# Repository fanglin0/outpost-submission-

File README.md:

# FIFA World Cup Player Love Compatibility Test

##  What this project is
Inspired by <a href="https://www.reddit.com/r/AustralianNostalgia/comments/1fx5e6g/old_school_love_compatibility_tests_random_i_know/">old school romance compaitbility tests (based on names)</a> I built a old-school style, hand-held console like hardware with Arduino 32 as the display to match the player to their soulmate (from the cast of the 2026 FIFA world cup players trending all over social media). With a series of personality questions the user will be matched to their perfect partner from the world cup, and be able to navigate and reset through answer choices with the buttons.

The Arduino handles the logic, the PCB wires everything together, and the OLED will display the game alongisde the buttons. 

## Project Architecture
                USB-C
                   │
                   ▼
        ┌─────────────────┐
        │ Arduino Nano    │
        │ ESP32           │
        │                 │
        │ Runs all code   │
        └─────────────────┘
           │  │  │  │
           │  │  │  │
           │  │  │  └── D5 → RESET button
           │  │  └───── D4 → RIGHT button
           │  └──────── D3 → OK button
           └─────────── D2 → LEFT button

           │
           ├── SDA → OLED SDA
           └── SCL → OLED SCL

           │
           ├── 5V → OLED VCC
           └── GND → OLED GND

## Software Flow 
Power On
   │
   ▼
Title Screen
   │
   ▼
Intro Screen
   │
   ▼
12 Quiz Questions
   │
   ▼
Fake Analysis Screen
   │
   ▼
Compatibility Result
   │
   ▼
Football Profile
   │
   ▼
Ending Screen
   │
   ▼
Reset

## Image examples and Demo
<a href="https://youtu.be/Up6vLfFCHvI">Video demo here</a>

---

## Why I made this project
To learn hardware in a unique project that I would enjoy using myself!

## How I made this project

Followed various tutorials for kicad, the C tutoial for eprosnality quiz to script the logic behind the love compatiblity quiz, and then learning how to use onshape to rig a simple 3d case to make the model resemble my vision of a handheld console more.

---

## Challenges I faced
Trying to get the LONG script to come together, had to troubleshoot various times
Also, trying to 3d model in onshape. I struggled to navigate the basic menu and a lot of parts in the project was harder than expected, as I had to learn them from scratch. It took a lot more cramming than expected to get in before deadline :')

##AI Declaration
ChatGPT was used to debug code when I got stuck, as I'm a complete beginner with almost no background in hardware.

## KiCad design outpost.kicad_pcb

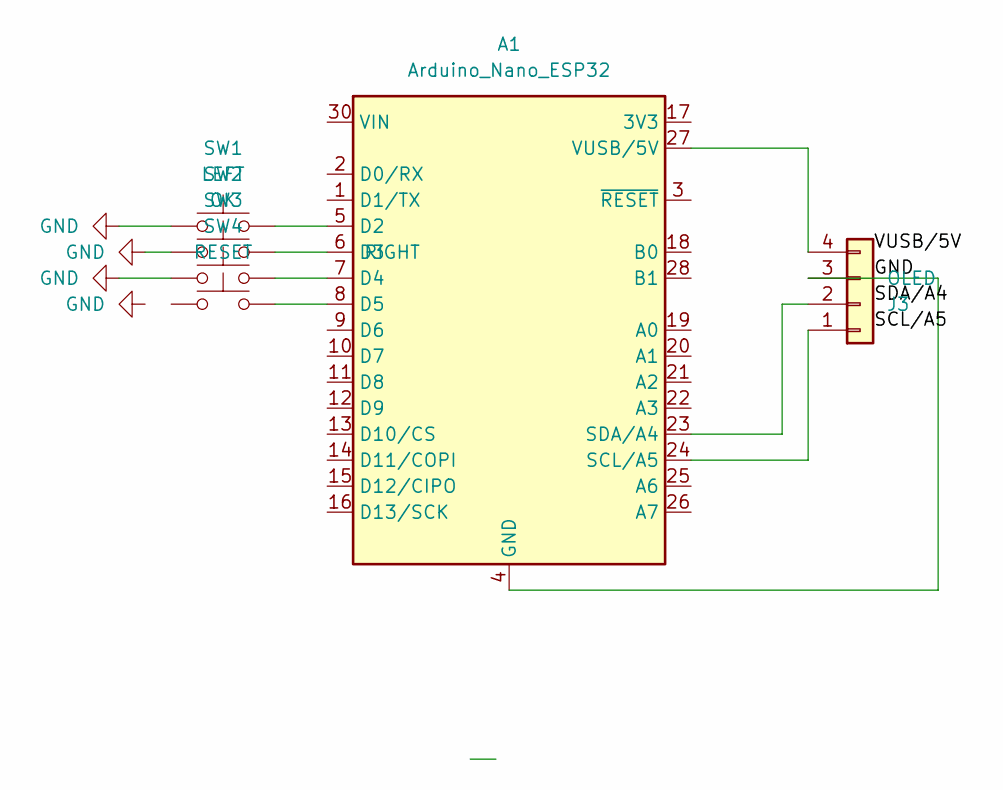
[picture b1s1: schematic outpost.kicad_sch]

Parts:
A1: Arduino_Nano_ESP32; PinHeader_2x15_P1.00mm_Horizontal
J3: OLED; FanPinHeader_1x04_P2.54mm_Vertical
SW1: LEFT; SW_PUSH_6mm
SW2: OK; SW_PUSH_6mm
SW3: RIGHT; SW_PUSH_6mm
SW4: RESET; SW_PUSH_6mm

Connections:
GND: A1.4 (GND), A1.29 (GND), J3.3, SW1.1, SW2.2, SW3.1
unnamed: A1.5 (D2), SW1.2
unnamed: A1.6 (D3), SW2.1
unnamed: A1.7 (D4), SW3.2
unnamed: A1.8 (D5), SW4.1 (1_1)
unnamed: A1.24 (SCL/A5), J3.1
unnamed: A1.23 (SDA/A4), J3.2
unnamed: A1.27 (VUSB/5V), J3.4

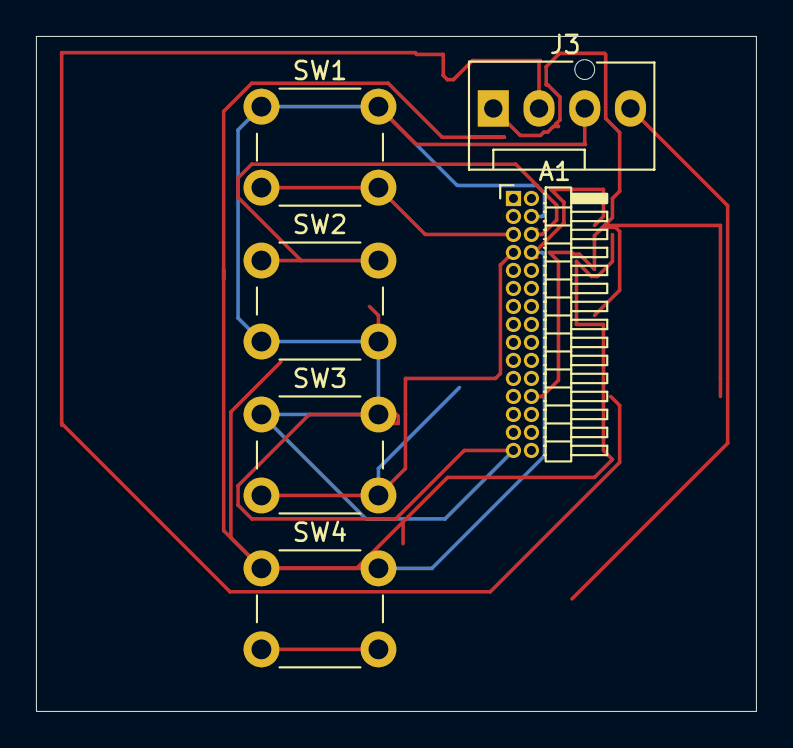
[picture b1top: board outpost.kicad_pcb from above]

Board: 2 copper layers, 40.0 x 37.5 mm, 6 parts (0 on the bottom side), 8 nets.
